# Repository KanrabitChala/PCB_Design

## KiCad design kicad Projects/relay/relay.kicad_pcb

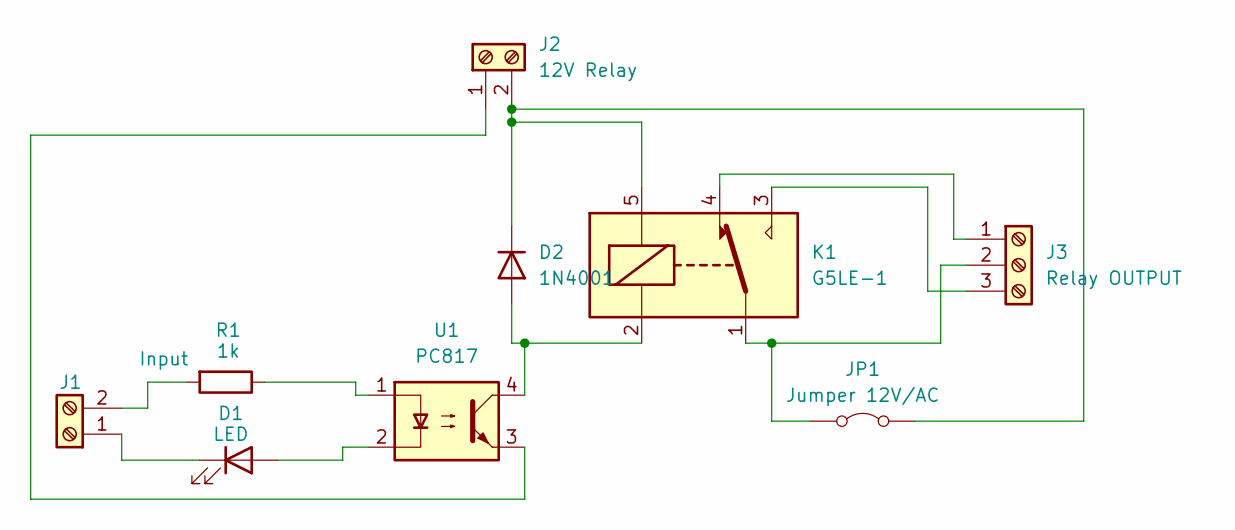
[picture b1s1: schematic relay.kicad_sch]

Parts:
D1: LED; LED_D3.0mm
D2: 1N4001; D_A-405_P7.62mm_Horizontal
J1: Input; TerminalBlock_Altech_AK300-2_P5.00mm
J2: 12V Relay; TerminalBlock_Altech_AK300-2_P5.00mm
J3: Relay OUTPUT; TerminalBlock_Altech_AK300-3_P5.00mm
JP1: Jumper 12V/AC; SolderJumper-2_P1.3mm_Open_RoundedPad1.0x1.5mm
K1: G5LE-1; Relay_SPDT_Omron-G5LE-1
R1: 1k; R_Axial_DIN0207_L6.3mm_D2.5mm_P10.16mm_Horizontal
U1: PC817; DIP-4_W7.62mm

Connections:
unnamed: D1.2 (A), U1.2
unnamed: D1.1 (K), J1.1
unnamed: D2.2 (A), K1.2, U1.4
unnamed: D2.1 (K), J2.2, JP1.2 (B), K1.5
unnamed: J1.2, R1.2
unnamed: J2.1, U1.3
unnamed: J3.1, K1.4
unnamed: J3.2, JP1.1 (A), K1.1
unnamed: J3.3, K1.3
unnamed: R1.1, U1.1

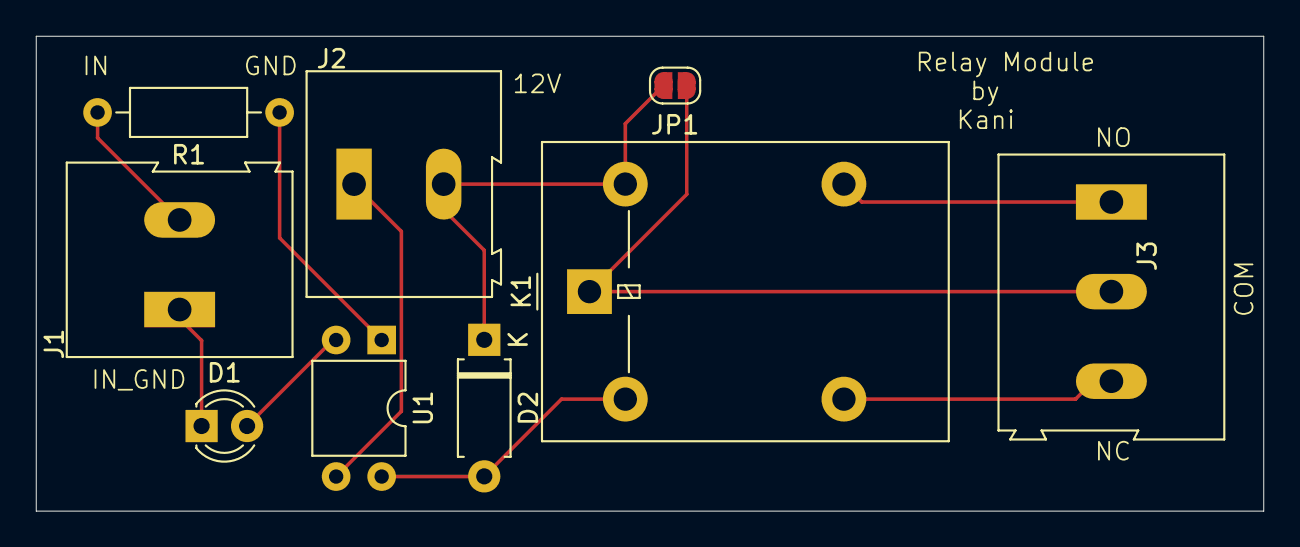
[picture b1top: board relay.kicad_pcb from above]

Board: 2 copper layers, 68.5 x 26.5 mm, 9 parts (0 on the bottom side), 10 nets.

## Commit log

2024-12-19 Create Proteus file
